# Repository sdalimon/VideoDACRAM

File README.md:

This is an adapter to add 512kB of SRAM and a simple video output to the Lattice MachXO3 starter board.

My original experiments used internal block RAM and a simple 2 resistor output that used the 75 ohm input of the TV.

As I got the resolution up the block RAM ran out, so this includes an SRAM.

The video out is now buffered and provides a proper 75 ohm output with an RCA socket.

Connect it to the J8 heade rof the dev board.

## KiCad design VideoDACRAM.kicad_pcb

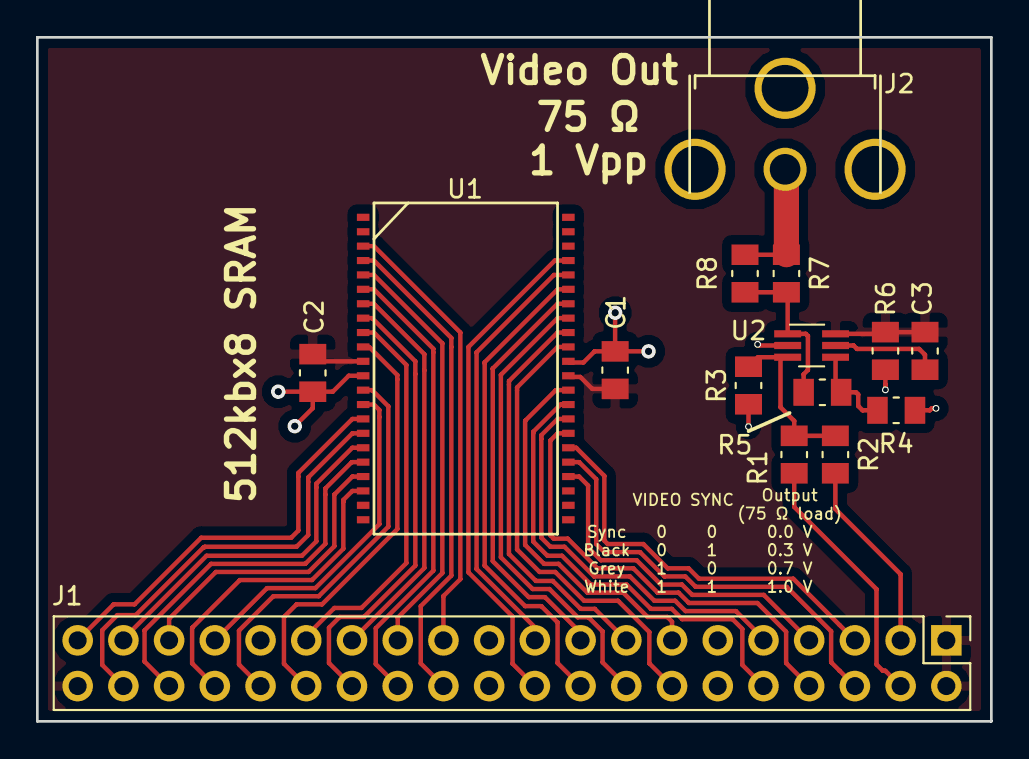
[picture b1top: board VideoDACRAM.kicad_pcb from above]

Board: 2 copper layers, 53.0 x 38.0 mm, 15 parts (0 on the bottom side), 39 nets.

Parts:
C1, C2, C3: 100n; C_0805_2012Metric_Pad1.15x1.50mm_HandSolder
J1: Conn_01x40; PinHeader_2x20_P2.54mm_Vertical
J2: RCJ-014
R1: 4k7; R_0805_2012Metric_Pad1.15x1.50mm_HandSolder
R2: 12k; R_0805_2012Metric_Pad1.15x1.50mm_HandSolder
R3: 1k5; R_0805_2012Metric_Pad1.15x1.50mm_HandSolder
R4, R5: 680; R_0805_2012Metric_Pad1.15x1.50mm_HandSolder
R6: 1k; R_0805_2012Metric_Pad1.15x1.50mm_HandSolder
R7: NI; R_0805_2012Metric_Pad1.15x1.50mm_HandSolder
R8: 75; R_0805_2012Metric_Pad1.15x1.50mm_HandSolder
U1: CY7C1049GN30-xxZSXI; TSOP 44 18.8x10.1x0.8
U2: LMH6601; SOT-363_SC-70-6_Handsoldering

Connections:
/SRAM_A0: J1.23, U1.3
/SRAM_A1: J1.24, U1.4
/SRAM_A2: J1.25, U1.5
/SRAM_A3: J1.26, U1.6
/SRAM_A4: J1.27, U1.7
/SRAM_A5: J1.38, U1.16
/SRAM_A6: J1.37, U1.17
/SRAM_A7: J1.36, U1.18
/SRAM_A8: J1.35, U1.19
/SRAM_A9: J1.34, U1.20
/SRAM_A10: J1.7, U1.26
/SRAM_A11: J1.6, U1.27
/SRAM_A12: J1.5, U1.28
/SRAM_A13: J1.8, U1.29
/SRAM_A14: J1.9, U1.30
/SRAM_A15: J1.17, U1.38
/SRAM_A16: J1.18, U1.39
/SRAM_A17: J1.19, U1.40
/SRAM_A18: J1.20, U1.41
/SRAM_D0: J1.29, U1.9
/SRAM_D1: J1.30, U1.10
/SRAM_D2: J1.32, U1.13
/SRAM_D3: J1.33, U1.14
/SRAM_D4: J1.10, U1.31
/SRAM_D5: J1.13, U1.32
/SRAM_D6: J1.14, U1.35
/SRAM_D7: J1.15, U1.36
/SRAM_~CE: J1.28, U1.8
/SRAM_~OE: J1.16, U1.37
/SRAM_~WE: J1.39, U1.15
/SYNC: J1.3, R2.2
/VIDEO: J1.4, R1.2
GND: C1.2, C2.2, C3.2, J1.11, J1.12, J1.21, J1.22, J1.31, J2.2, R3.1, R4.1, U1.12, U1.34, U2.2
unnamed: J2.1, R7.1, R8.1
unnamed: R1.1, R2.1, R3.2, U2.3
unnamed: R4.2, R5.2, U2.4
unnamed: R5.1, R7.2, R8.2, U2.1
unnamed: R6.1, U2.5
VDD: C1.1, C2.1, C3.1, J1.1, J1.2, J1.40, R6.2, U1.11, U1.33, U2.6
